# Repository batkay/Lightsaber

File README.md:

# Lightsaber
Repository for custom lightsaber PCB and firmware
## Overview
The firmware folder contains the STMCubeIDE project used to program the STM32F446RE, and the LightsaberDesign folder contains the KiCad project for the PCB used. The Outputs folder contains the outputs from KiCad that was sent to JLCPCB for assembly. The project has been changed since Outputs was last updated, so the folder is not up to date. SpiceSimulations contains the LTSpice simulations used when designing the PCB.
## Obtaining audio
The audio file was obtained by taking a wav file from online, importing it into Audacity, then exporting it as a monochannel 8-bit audio file at 8000Hz. This then allowed the file to be played with interrupts instead of using a DMA.
## Known Issues
When playing audio from the speaker, the noise is extremely noisy. The source of this noise is not currently known, but it is likely due to a hardware issue, as the original noise file can very faintly be heard in the noise.

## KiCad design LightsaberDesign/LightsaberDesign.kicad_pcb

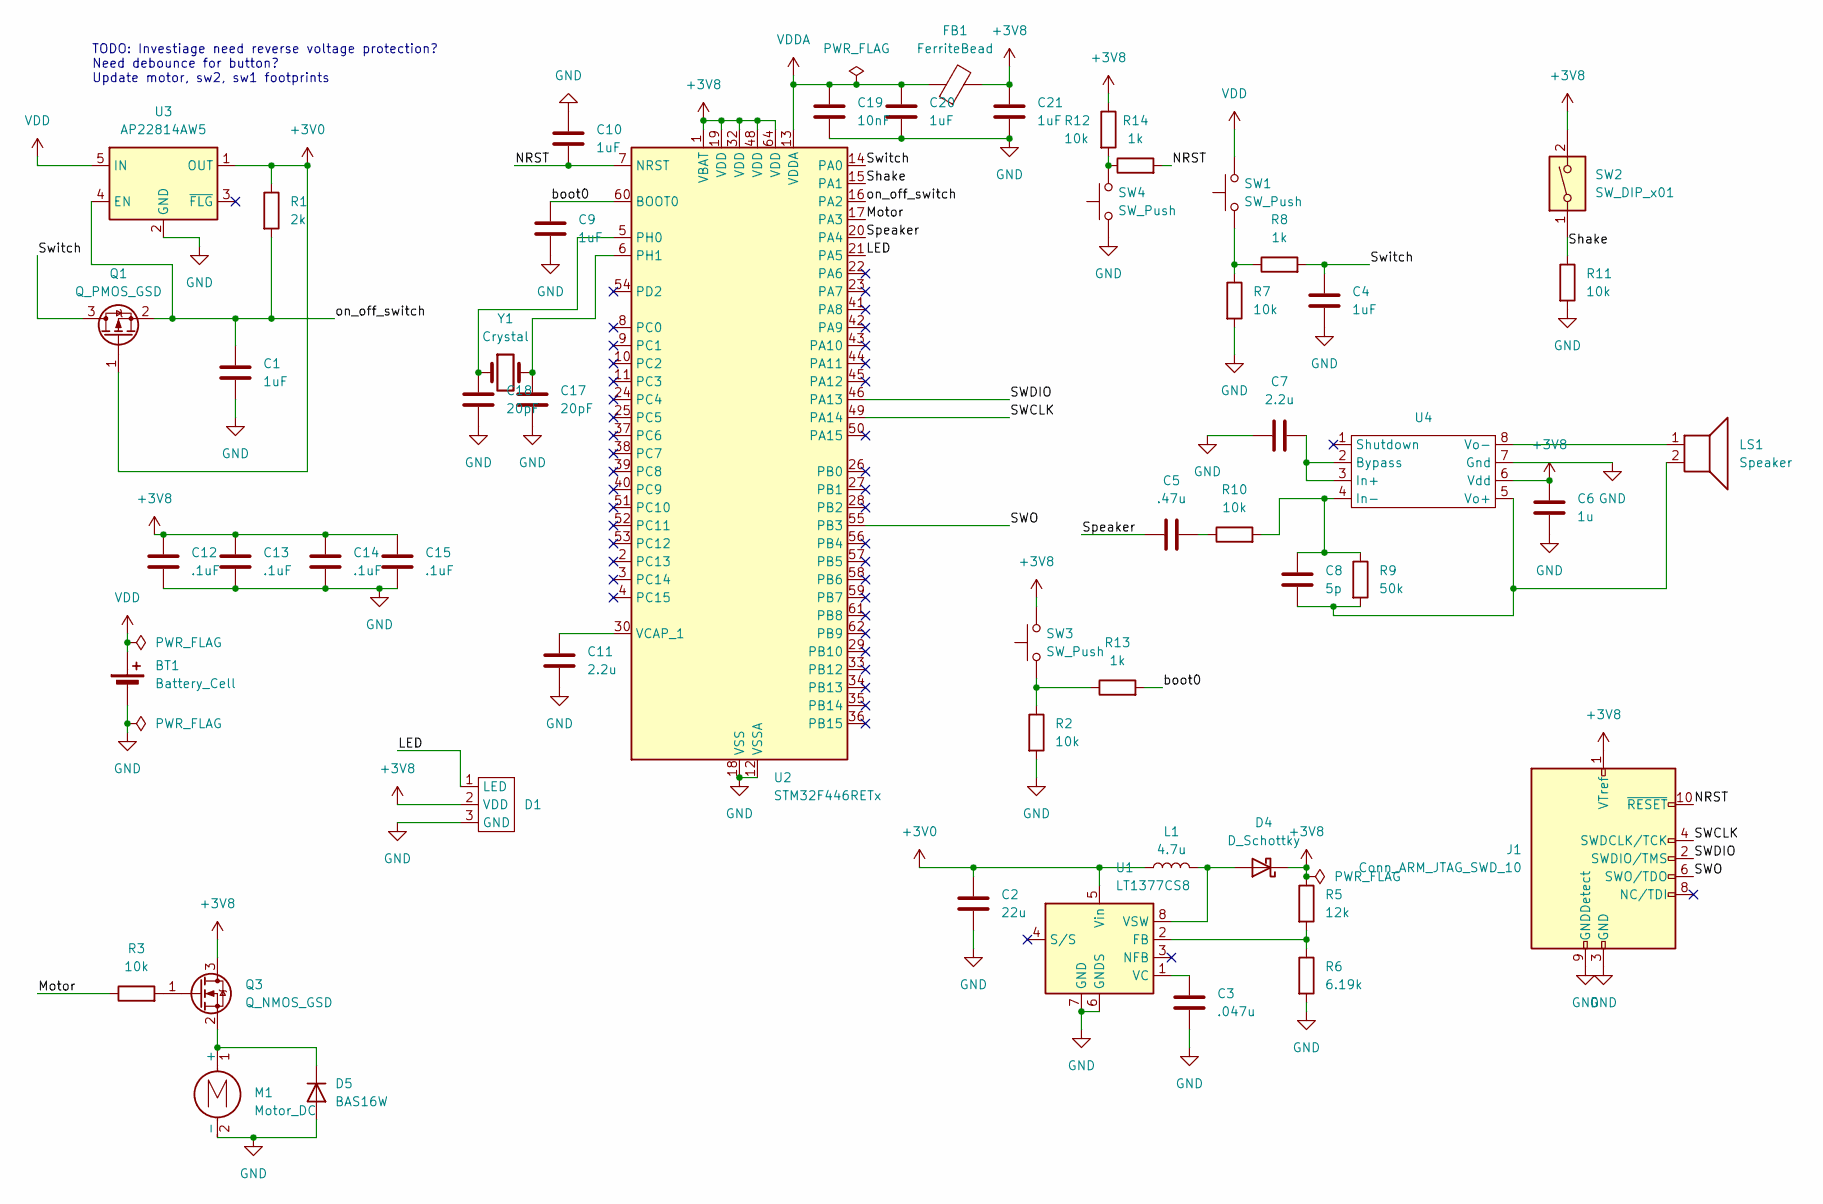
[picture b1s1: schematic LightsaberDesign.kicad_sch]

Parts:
BT1: Battery_Cell; JST_PH_B2B-PH-K_1x02_P2.00mm_Vertical
C1, C4, C9, C10, C20, C21: 1uF; C_0805_2012Metric_Pad1.18x1.45mm_HandSolder
C2: 22u; C_0805_2012Metric_Pad1.18x1.45mm_HandSolder
C3: .047u; C_0805_2012Metric_Pad1.18x1.45mm_HandSolder
C5: .47u; C_0805_2012Metric_Pad1.18x1.45mm_HandSolder
C6: 1u; C_0805_2012Metric_Pad1.18x1.45mm_HandSolder
C7, C11: 2.2u; C_0805_2012Metric_Pad1.18x1.45mm_HandSolder
C8: 5p; C_0805_2012Metric_Pad1.18x1.45mm_HandSolder
C12, C13, C14, C15: .1uF; C_0805_2012Metric_Pad1.18x1.45mm_HandSolder
C17, C18: 20pF; C_0805_2012Metric_Pad1.18x1.45mm_HandSolder
C19: 10nF; C_0805_2012Metric_Pad1.18x1.45mm_HandSolder
D1: JST_PH_B3B-PH-K_1x03_P2.00mm_Vertical
D4: D_Schottky; D_SOD-323_HandSoldering
D5: BAS16W; SOT-323_SC-70
FB1: FerriteBead; C_0805_2012Metric_Pad1.18x1.45mm_HandSolder
J1: Conn_ARM_JTAG_SWD_10; Samtec_HLE-105-02-xxx-DV_2x05_P2.54mm_Horizontal
L1: 4.7u; L_0805_2012Metric_Pad1.15x1.40mm_HandSolder
LS1: Speaker; Molex_PicoBlade_53047-0210_1x02_P1.25mm_Vertical
M1: Motor_DC; Molex_PicoBlade_53047-0210_1x02_P1.25mm_Vertical
Q1: Q_PMOS_GSD; TSOT-23_HandSoldering
Q3: Q_NMOS_GSD; SOT-23-3
R1: 2k; R_0805_2012Metric_Pad1.20x1.40mm_HandSolder
R2, R3, R7, R10, R11, R12: 10k; R_0805_2012Metric_Pad1.20x1.40mm_HandSolder
R5: 12k; R_0805_2012Metric_Pad1.20x1.40mm_HandSolder
R6: 6.19k; R_0805_2012Metric_Pad1.20x1.40mm_HandSolder
R8, R13, R14: 1k; R_0805_2012Metric_Pad1.20x1.40mm_HandSolder
R9: 50k; R_0805_2012Metric_Pad1.20x1.40mm_HandSolder
SW1: SW_Push; PinHeader_1x02_P2.54mm_Vertical
SW2: SW_DIP_x01; CP_Radial_D4.0mm_P1.50mm
SW3, SW4: SW_Push; SW_PUSH_6mm
U1: LT1377CS8; SOIC-8_3.9x4.9mm_P1.27mm
U2: STM32F446RETx; LQFP-64_10x10mm_P0.5mm
U3: AP22814AW5; SOT-23-5
U4: SOIC-8_3.9x4.9mm_P1.27mm
Y1: Crystal; Crystal_SMD_HC49-SD

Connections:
+3V0: C2.1, L1.1, Q1.1 (G), R1.1, U1.5 (Vin), U3.1 (OUT)
+3V8: C6.1, C12.1, C13.1, C14.1, C15.1, C21.1, D1.2 (VDD), D4.1 (K), FB1.2, J1.1 (VTref), Q3.3 (D), R5.1, R12.1, SW2.2, SW3.2, U2.1 (VBAT), U2.19 (VDD), U2.32 (VDD), U2.48 (VDD), U2.64 (VDD), U4.6 (Vdd)
/LED: D1.1 (LED), U2.21 (PA5)
/Motor: R3.1, U2.17 (PA3)
/NRST: C10.2, J1.10 (~RESET), R14.2, U2.7 (NRST)
/SWCLK: J1.4 (SWDCLK/TCK), U2.49 (PA14)
/SWDIO: J1.2 (SWDIO/TMS), U2.46 (PA13)
/SWO: J1.6 (SWO/TDO), U2.55 (PB3)
/Shake: R11.1, SW2.1, U2.15 (PA1)
/Speaker: C5.1, U2.20 (PA4)
/Switch: C4.1, Q1.3 (D), R8.2, U2.14 (PA0)
/boot0: C9.1, R13.2, U2.60 (BOOT0)
/on_off_switch: C1.1, Q1.2 (S), R1.2, U2.16 (PA2), U3.4 (EN)
GND: BT1.2 (-), C1.2, C2.2, C3.2, C4.2, C6.2, C7.2, C9.2, C10.1, C11.2, C12.2, C13.2, C14.2, C15.2, C17.2, C18.2, C19.2, C20.2, C21.2, D1.3 (GND), D5.1 (A), J1.3 (GND), J1.5 (GND), J1.9 (GNDDetect), M1.2 (-), R2.2, R6.2, R7.2, R11.2, SW4.1, U1.6 (GNDS), U1.7 (GND), U2.12 (VSSA), U2.18 (VSS), U2.31 (VSS), U2.47 (VSS), U2.63 (VSS), U3.2 (GND), U4.7 (Gnd)
unnamed: C5.2, R10.1
unnamed: D4.2 (A), L1.2, U1.8 (VSW)
unnamed: D5.3 (K), M1.1 (+), Q3.2 (S)
unnamed: Q3.1 (G), R3.2
unnamed: R7.1, R8.1, SW1.1
unnamed: R12.2, R14.1, SW4.2
unnamed: R2.1, R13.1, SW3.1
unnamed: R5.2, R6.1, U1.2 (FB)
unnamed: C3.1, U1.1 (VC)
unnamed: C18.1, U2.5 (PH0), Y1.1
unnamed: C17.1, U2.6 (PH1), Y1.2
unnamed: C11.1, U2.30 (VCAP_1)
unnamed: C7.1, U4.2 (Bypass), U4.3 (In+)
unnamed: C8.2, R9.1, R10.2, U4.4 (In-)
unnamed: C8.1, LS1.2, R9.2, U4.5 (Vo+)
unnamed: LS1.1, U4.8 (Vo-)
VDD: BT1.1 (+), SW1.2, U3.5 (IN)
VDDA: C19.1, C20.1, FB1.1, U2.13 (VDDA)

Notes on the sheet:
TODO: Investiage need reverse voltage protection? Need debounce for button? Update motor, sw2, sw1 footprints

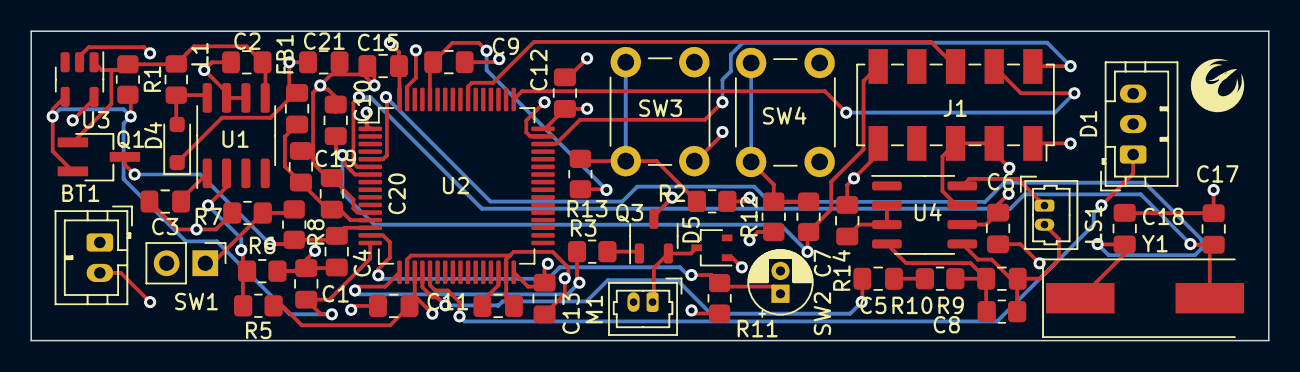
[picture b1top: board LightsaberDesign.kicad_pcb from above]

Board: 4 copper layers, 81.3 x 20.3 mm, 53 parts (0 on the bottom side), 32 nets.

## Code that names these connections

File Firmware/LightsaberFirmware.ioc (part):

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Mcu.Name=STM32F446R(C-E)Tx
Mcu.Package=LQFP64
Mcu.UserName=STM32F446RETx
PA0-WKUP.Signal=GPIO_Input
PA1.Signal=GPIO_Input
PA13.Mode=Trace_Asynchronous_SW
PA13.Signal=SYS_JTMS-SWDIO
PA14.Mode=Trace_Asynchronous_SW
PA14.Signal=SYS_JTCK-SWCLK
PA2.GPIOParameters=PinState
PA2.PinState=GPIO_PIN_SET
PA2.Signal=GPIO_Output
PA3.Signal=S_TIM5_CH4
PA4.Signal=COMP_DAC1_group
PA5.Signal=S_TIM2_CH1_ETR
PB3.Mode=Trace_Asynchronous_SW
PB3.Signal=SYS_JTDO-SWO
PH0-OSC_IN.Mode=HSE-External-Oscillator
PH0-OSC_IN.Signal=RCC_OSC_IN
PH1-OSC_OUT.Mode=HSE-External-Oscillator
PH1-OSC_OUT.Signal=RCC_OSC_OUT
RCC.HSE_VALUE=8000000
board=custom

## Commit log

2024-05-14 Initial
2024-05-14 Added firmware repo
2024-06-17 Setup schematic circuit for ship mode and connectors
2024-06-18 Added button debounce, made buck 3.7v
2024-06-22 New speaker module
2024-06-23 Layed out pcb
2024-06-29 Added crystal, ferrite bead
2024-07-02 Finished drc
2024-07-02 Updated capacitor values
2024-07-29 Simple Neopixel driver added
2024-08-06 Minimum working firmware
2024-08-07 Added motor rumble, started to add audio
2024-08-08 Startup animation
2024-08-08 Updated PCB with new header
2024-08-13 Updated documentation
